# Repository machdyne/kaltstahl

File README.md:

# Kaltstahl Storage Device

Kaltstahl is a higher capacity version of [Blaustahl](https://github.com/machdyne/blaustahl).

## Firmware

Kaltstahl can use either the Blaustahl (USB-CDC) or [Ebenstahl](https://github.com/machdyne/ebenstahl) (USB-MSC) firmware.

The default firmware images are [available here](firmware).

Please see the [Blaustahl](https://github.com/machdyne/blaustahl) repo for instructions and firmware source code for the USB-CDC firmware.

To build the firmware from the source code, you will need to modify blaustahl.h and change the FRAM\_SIZE value to 262144 and then use the following commands:

```
$ mkdir build
$ cd build
$ cmake -DPICO_DEFAULT_BOOT_STAGE2_FILE=/your-pico-sdk-directory/pico-sdk/src/rp2040/boot_stage2/boot2_generic_03h.S ..
$ make
```

## License

The contents of this repo are released under the [Lone Dynamics Open License](LICENSE.md).

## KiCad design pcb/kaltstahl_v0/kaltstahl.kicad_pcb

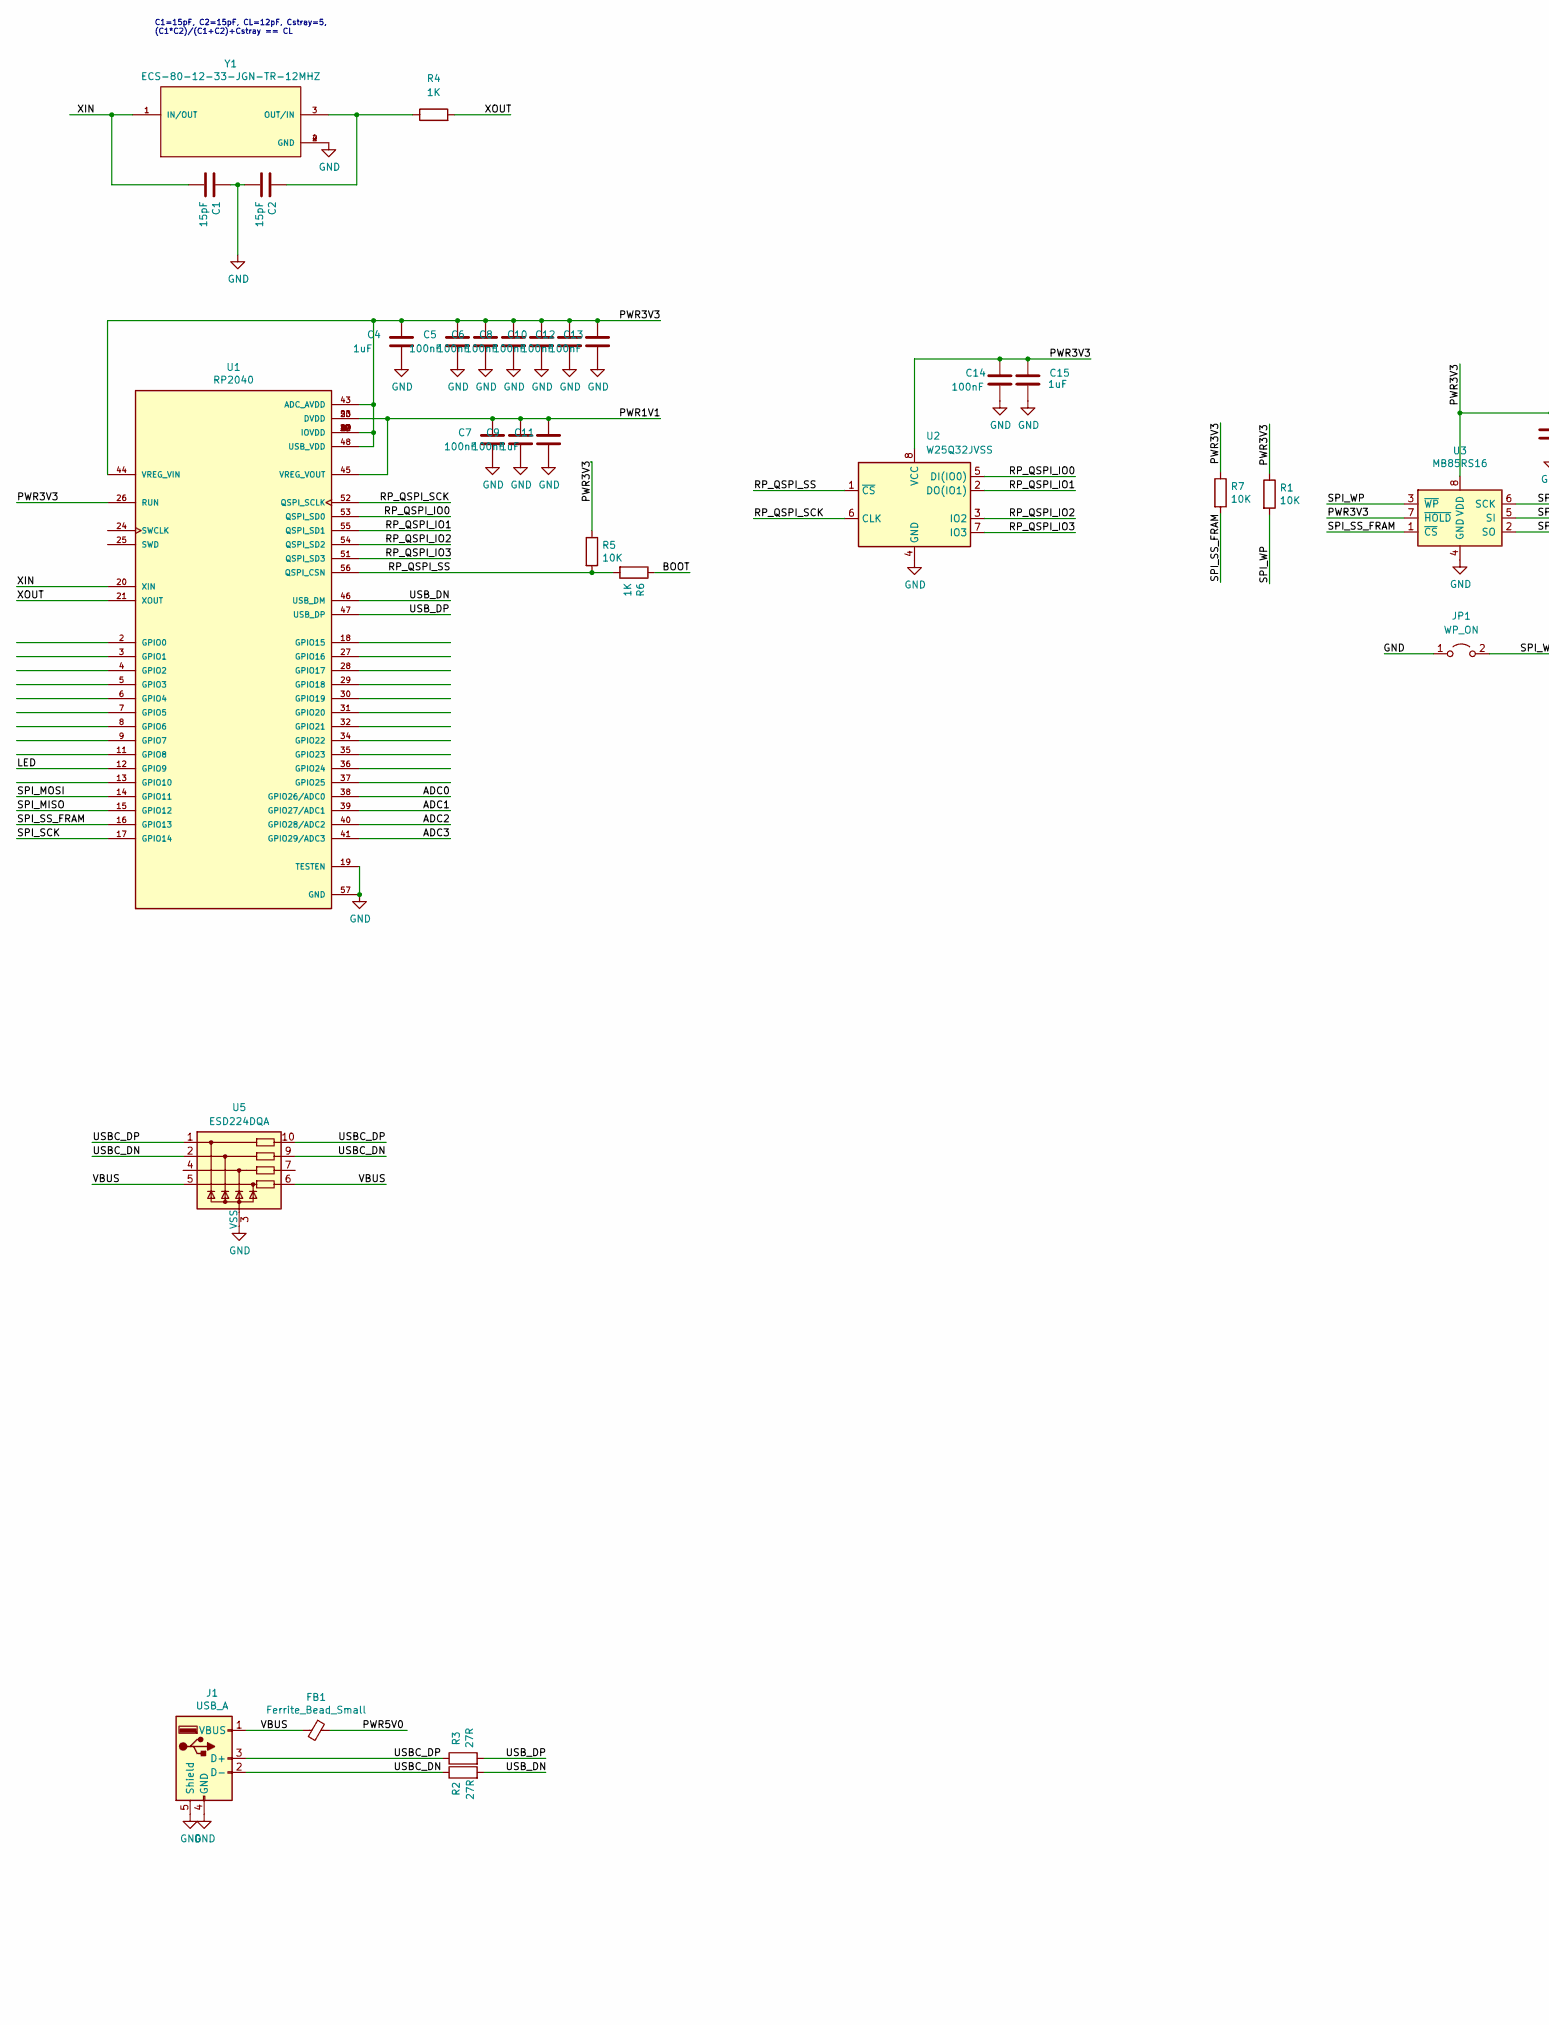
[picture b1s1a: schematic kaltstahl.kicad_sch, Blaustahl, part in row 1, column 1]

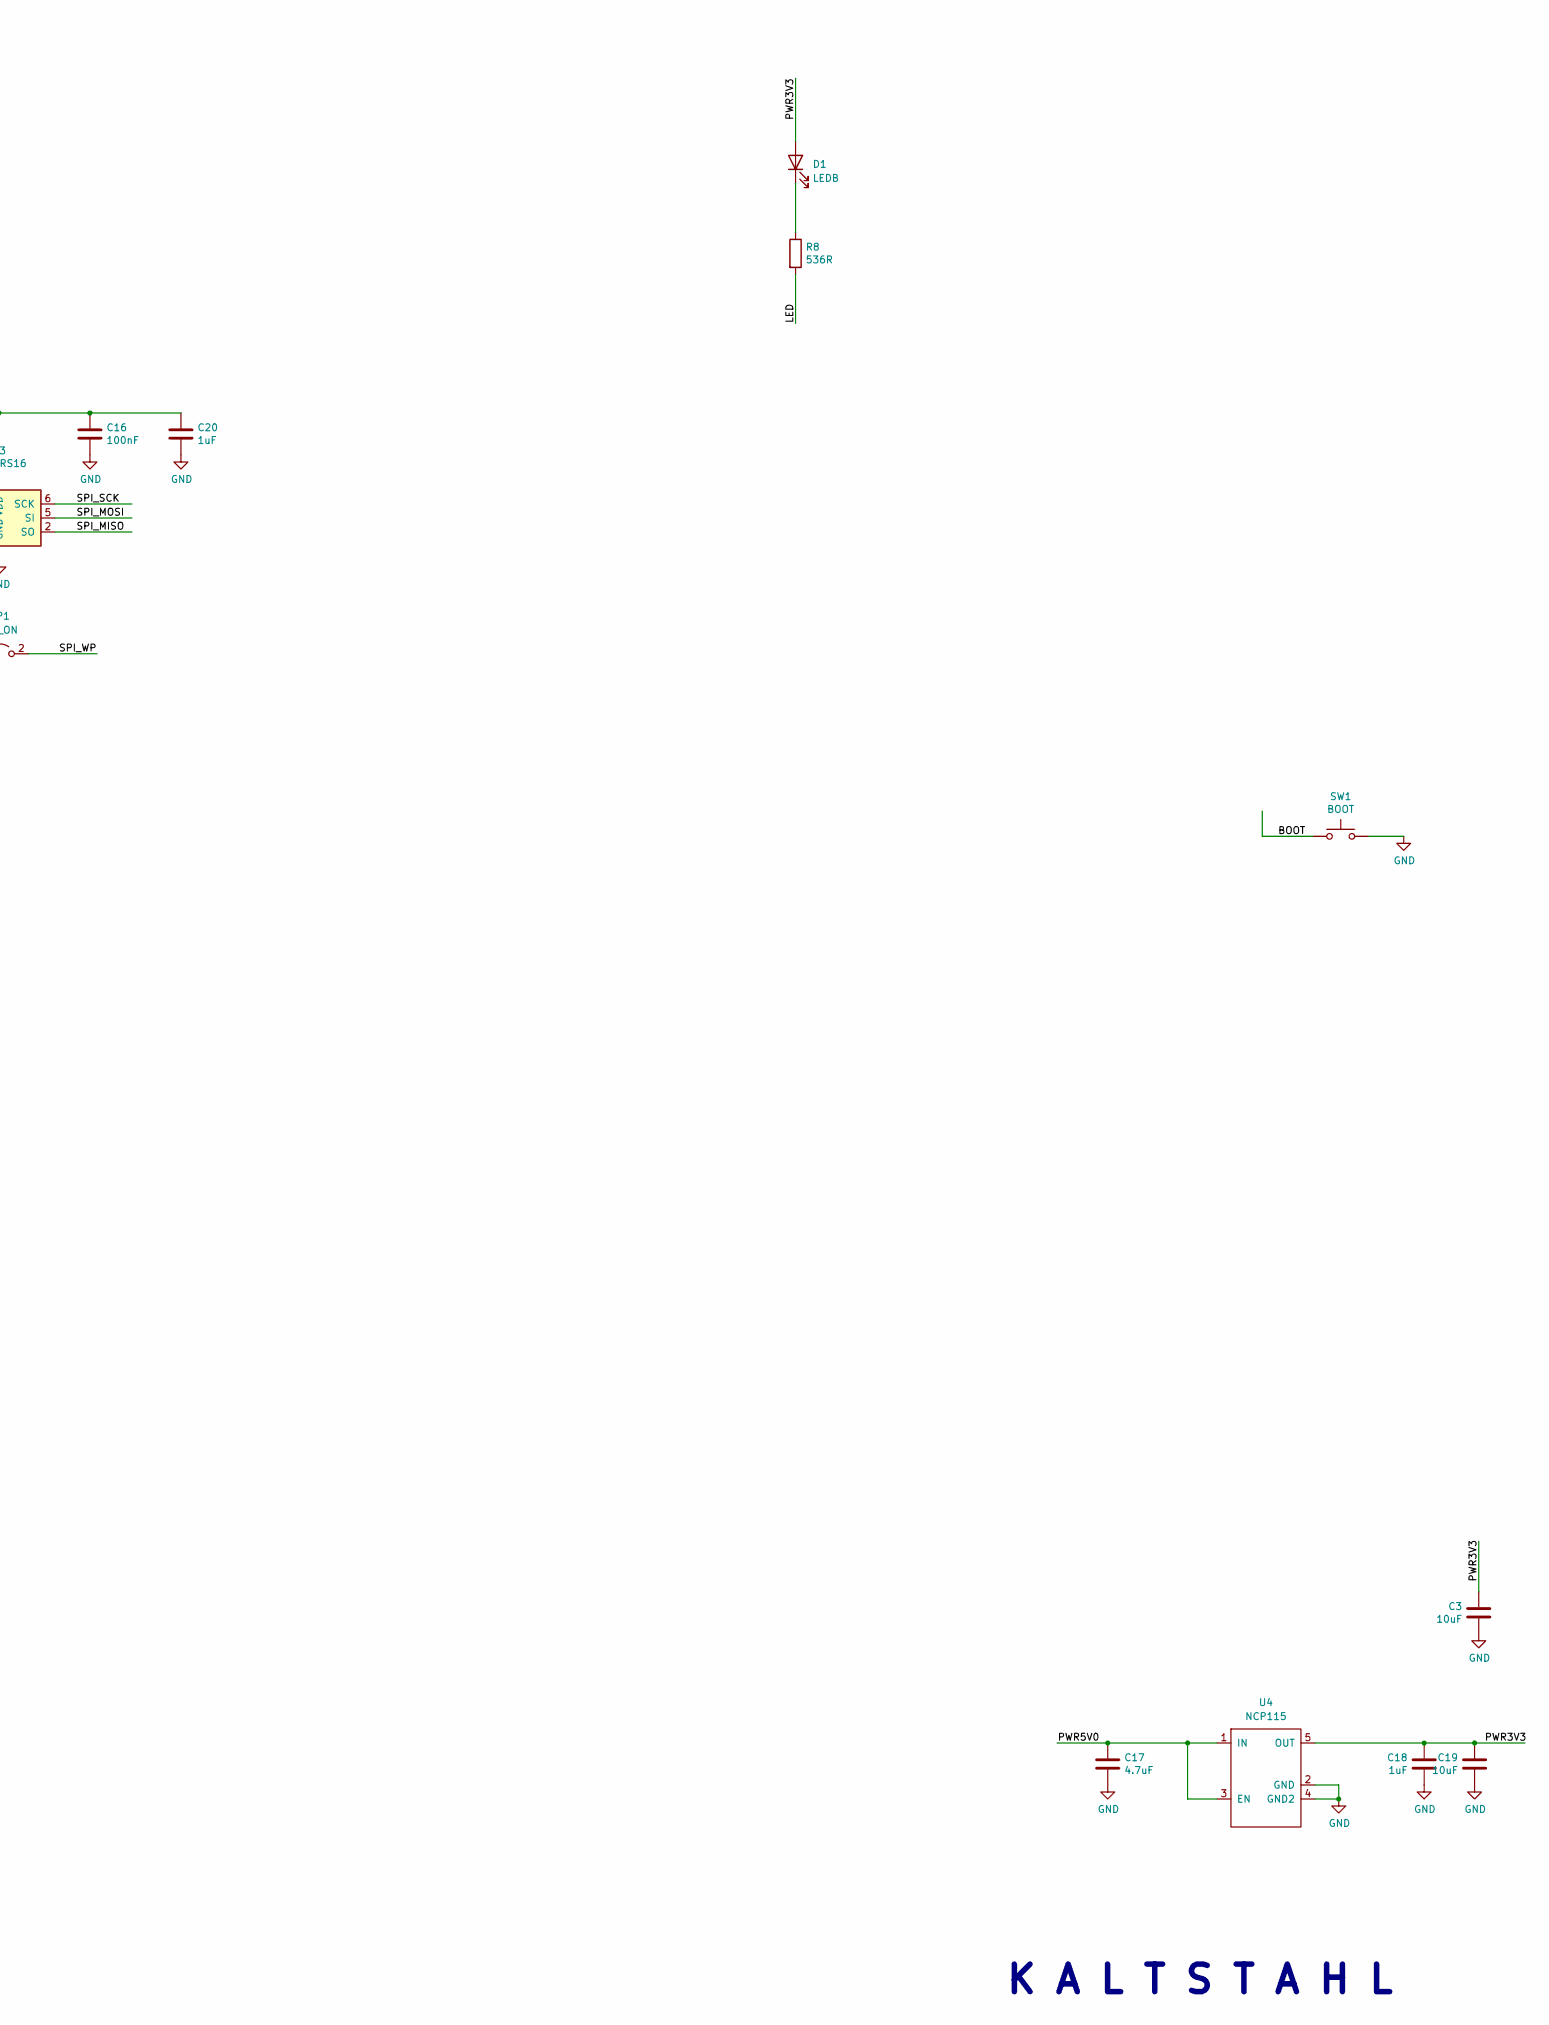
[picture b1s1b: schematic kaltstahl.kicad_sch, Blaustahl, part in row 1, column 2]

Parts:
C1, C2: 15pF; C_0402_1005Metric
C3, C19: 10uF; C_0402_1005Metric
C4, C11, C15, C18, C20: 1uF; C_0402_1005Metric
C5, C6, C7, C8, C9, C10, C12, C13, C14, C16: 100nF; C_0402_1005Metric
C17: 4.7uF; C_0402_1005Metric
D1: LEDB; LED_0603_1608Metric
FB1: Ferrite_Bead_Small; R_0402_1005Metric
J1: USB_A; USB_A_CNCTech_1001-011-01101_Horizontal
JP1: WP_ON; SolderJumper-2_P1.3mm_Open_Pad1.0x1.5mm
R1, R5, R7: 10K; R_0402_1005Metric
R2, R3: 27R; R_0402_1005Metric
R4, R6: 1K; R_0402_1005Metric
R8: 536R; R_0402_1005Metric
SW1: BOOT; Button_2P_3x4mm
U1: RP2040; RP2040-QFN-56-OFFICIAL; PARTREV 1.6.1
U2: W25Q32JVSS; SOIC-8_3.9x4.9mm_P1.27mm
U3: MB85RS16; SOIC-8_3.9x4.9mm_P1.27mm
U4: NCP115; TSOP-5_1.65x3.05mm_P0.95mm
U5: ESD224DQA; Diodes_UDFN-10_1.0x2.5mm_P0.5mm
Y1: ECS-80-12-33-JGN-TR-12MHZ; XTAL_ECS-240-8-33-AGN-TR

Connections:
/ADC0: U1.38 (GPIO26/ADC0)
/ADC1: U1.39 (GPIO27/ADC1)
/ADC2: U1.40 (GPIO28/ADC2)
/ADC3: U1.41 (GPIO29/ADC3)
/BOOT: R6.1, SW1.1
/LED: R8.2, U1.12 (GPIO9)
/PWR1V1: C7.1, C9.1, C11.1, U1.23 (DVDD), U1.45 (VREG_VOUT), U1.50 (DVDD)
/PWR3V3: C3.1, C4.1, C5.1, C6.1, C8.1, C10.1, C12.1, C13.1, C14.1, C15.1, C16.1, C18.1, C19.1, C20.1, D1.2 (A), R1.1, R5.1, R7.1, U1.1 (IOVDD), U1.10 (IOVDD), U1.22 (IOVDD), U1.26 (RUN), U1.33 (IOVDD), U1.42 (IOVDD), U1.43 (ADC_AVDD), U1.44 (VREG_VIN), U1.48 (USB_VDD), U1.49 (IOVDD), U2.8 (VCC), U3.7 (~HOLD), U3.8 (VDD), U4.5 (OUT)
/PWR5V0: C17.1, FB1.1, U4.1 (IN), U4.3 (EN)
/RP_QSPI_IO0: U1.53 (QSPI_SD0), U2.5 (DI(IO0))
/RP_QSPI_IO1: U1.55 (QSPI_SD1), U2.2 (DO(IO1))
/RP_QSPI_IO2: U1.54 (QSPI_SD2), U2.3 (IO2)
/RP_QSPI_IO3: U1.51 (QSPI_SD3), U2.7 (IO3)
/RP_QSPI_SCK: U1.52 (QSPI_SCLK), U2.6 (CLK)
/RP_QSPI_SS: R5.2, R6.2, U1.56 (QSPI_CSN), U2.1 (~CS)
/SPI_MISO: U1.15 (GPIO12), U3.2 (SO)
/SPI_MOSI: U1.14 (GPIO11), U3.5 (SI)
/SPI_SCK: U1.17 (GPIO14), U3.6 (SCK)
/SPI_SS_FRAM: R7.2, U1.16 (GPIO13), U3.1 (~CS)
/SPI_WP: JP1.2 (B), R1.2, U3.3 (~WP)
/USBC_DN: J1.2 (D-), R2.1, U5.2, U5.9
/USBC_DP: J1.3 (D+), R3.1, U5.1, U5.10
/USB_DN: R2.2, U1.46 (USB_DM)
/USB_DP: R3.2, U1.47 (USB_DP)
/VBUS: FB1.2, J1.1 (VBUS), U5.5, U5.6
/XIN: C1.2, U1.20 (XIN), Y1.1 (IN/OUT)
/XOUT: R4.2, U1.21 (XOUT)
GND: C1.1, C2.2, C3.2, C4.2, C5.2, C6.2, C7.2, C8.2, C9.2, C10.2, C11.2, C12.2, C13.2, C14.2, C15.2, C16.2, C17.2, C18.2, C19.2, C20.2, J1.4 (GND), J1.5 (Shield), JP1.1 (A), SW1.2, U1.19 (TESTEN), U1.57 (GND), U2.4 (GND), U3.4 (GND), U4.2 (GND), U4.4 (GND2), U5.3 (VSS), U5.8 (VSS), Y1.2 (GND), Y1.4 (GND)
unnamed: D1.1 (K), R8.1
unnamed: C2.1, R4.1, Y1.3 (OUT/IN)

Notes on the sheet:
C1=15pF, C2=15pF, CL=12pF, Cstray=5, (C1*C2)/(C1+C2)+Cstray == CL
K A L T S T A H L

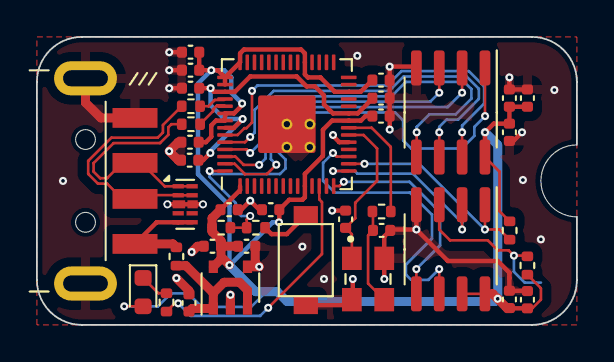
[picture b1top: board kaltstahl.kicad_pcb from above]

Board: 2 copper layers, 30.0 x 16.0 mm, 39 parts (1 on the bottom side), 26 nets.

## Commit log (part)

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2025-02-02 add v0 schematics
2025-02-11 firmware 0.0.8
2025-08-23 msc firmware
2025-12-10 add pcb
2026-06-19 add new case design

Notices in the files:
pcb/kaltstahl_v0/kaltstahl.kicad_sch:
Copyright © 2024 Lone Dynamics Corporation
